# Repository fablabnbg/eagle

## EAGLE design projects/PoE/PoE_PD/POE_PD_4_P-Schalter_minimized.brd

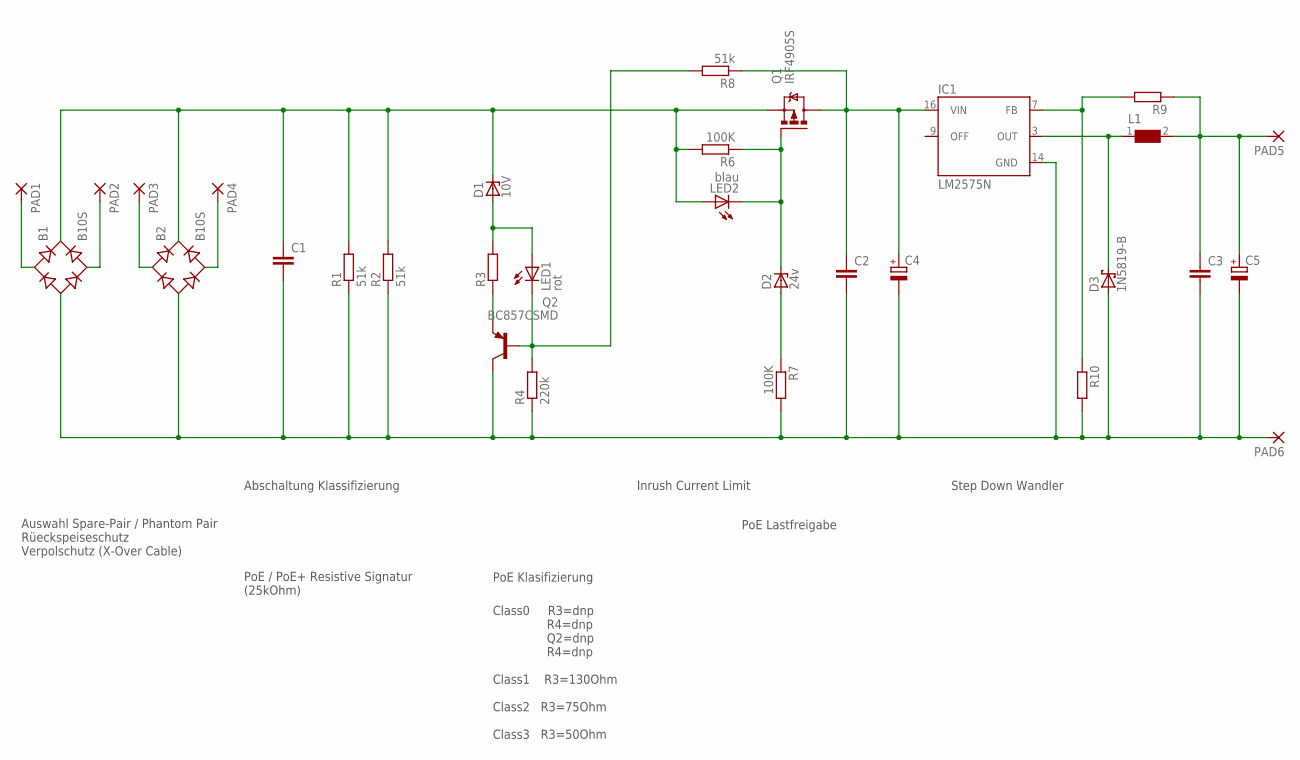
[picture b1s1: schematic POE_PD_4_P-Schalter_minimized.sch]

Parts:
B1, B2: B10S; MBS
C1, C2, C3: C-EUC0805; C0805
C4, C5: CPOL-EUE2.5-5; E2,5-5
D1: 10V; SOT23
D2: 24v; SOT23
D3: 1N5819-B; DO41-7.6
IC1: LM2575N; DIL16
L1: WE-PD2_S
LED1: rot; CHIP-LED0805
LED2: blau; CHIP-LED0805
PAD1, PAD2, PAD3, PAD4, PAD5, PAD6: 2,15/1,0
Q1: IRF4905S; D-PAK_TO252AA
Q2: BC857CSMD; SOT23-BEC
R1, R2, R8: 51k; R0603
R3, R9, R10: R-EU_0207/7; 0207/7
R4: 220k; R0603
R6, R7: 100K; R0603

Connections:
unnamed: B1.-, B2.-, C1.2, C2.2, C3.2, C4.-, C5.-, D3.A, IC1.14 (GND), PAD6.1, Q2.C, R1.1, R2.1, R4.1, R7.2, R10.2
unnamed: Q2.E, R3.1
unnamed: B1.AC1, PAD1.1
unnamed: LED1.C, Q2.B, R4.2, R8.2
unnamed: D1.1 (A), LED1.A, R3.2
unnamed: D2.1 (A), R7.1
unnamed: B1.+, B2.+, C1.1, D1.3 (C), LED2.A, Q1.3 (S), R1.2, R2.2, R6.2
unnamed: D2.3 (C), LED2.C, Q1.1 (G), R6.1
unnamed: D3.C, IC1.3 (OUT), L1.1
unnamed: C3.1, C5.+, L1.2, PAD5.1, R9.1
unnamed: C2.1, C4.+, IC1.16 (VIN), Q1.4 (D), R8.1
unnamed: IC1.7 (FB), R9.2, R10.1
unnamed: B1.AC2, PAD2.1
unnamed: B2.AC1, PAD3.1
unnamed: B2.AC2, PAD4.1

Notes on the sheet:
Auswahl Spare-Pair / Phantom Pair Rüeckspeiseschutz Verpolschutz (X-Over Cable)
Abschaltung Klassifizierung
PoE / PoE+ Resistive Signatur (25kOhm)
PoE Klasifizierung
Inrush Current Limit
PoE Lastfreigabe
Step Down Wandler
Class0 R3=dnp R4=dnp Q2=dnp R4=dnp Class1 R3=130Ohm Class2 R3=75Ohm Class3 R3=50Ohm

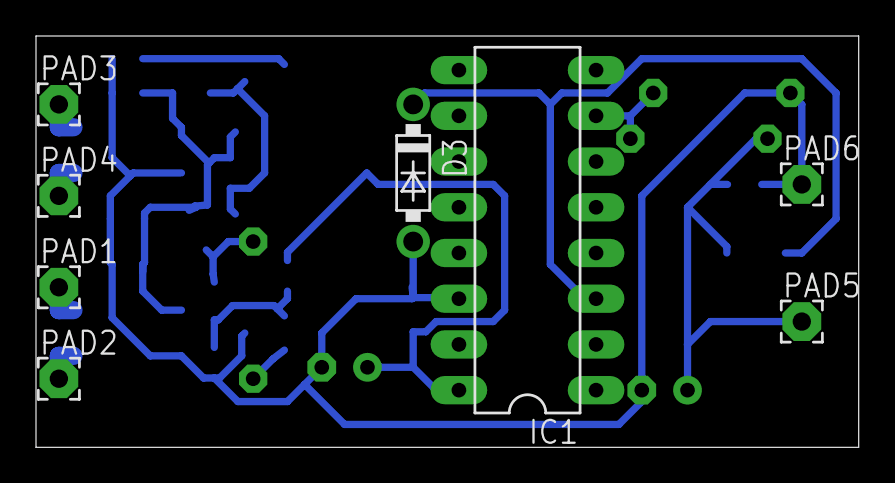
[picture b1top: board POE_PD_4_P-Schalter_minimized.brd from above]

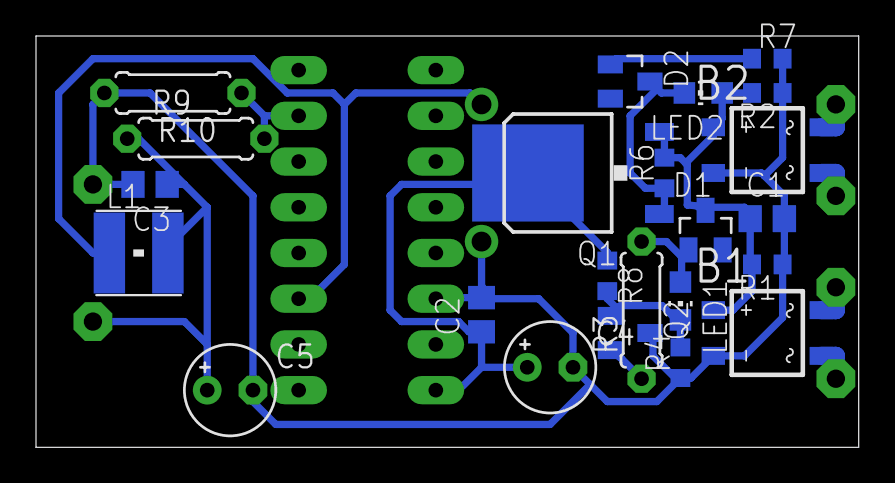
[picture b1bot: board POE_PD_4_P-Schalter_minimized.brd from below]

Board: 2 copper layers, 45.7 x 22.8 mm, 31 parts (23 on the bottom side), 15 nets.

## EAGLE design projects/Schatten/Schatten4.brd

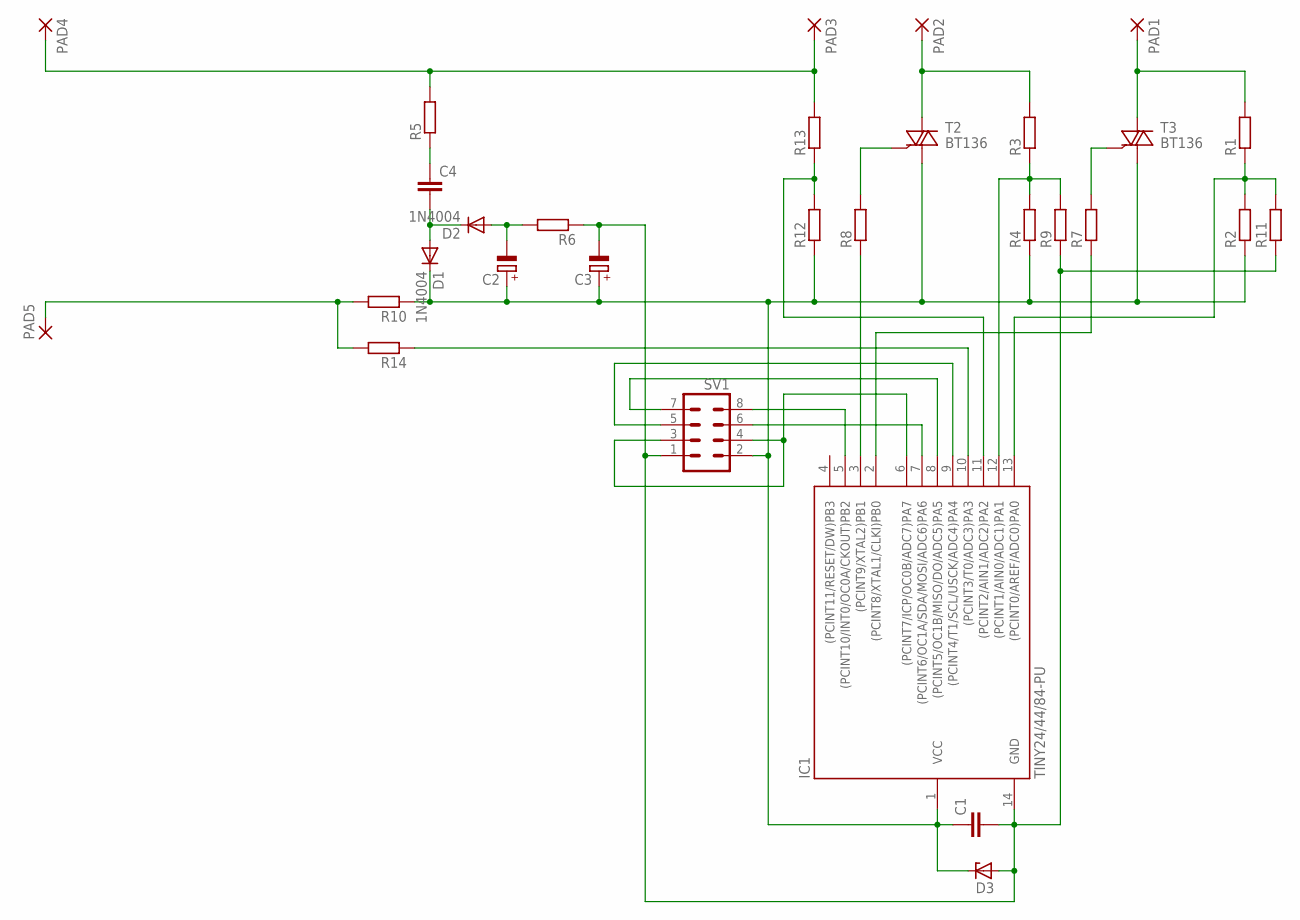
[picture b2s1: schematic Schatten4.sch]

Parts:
C1: C-EUC3225; C3225
C2, C3: CPOL-EUE5-8.5; E5-8,5
C4: C-EU150-064X183; C150-064X183
D1, D2: 1N4004; DO41-10
D3: ZENER-DIODEZD-7.5; ZDIO-7.5
IC1: TINY24/44/84-PU; DIL14
PAD1, PAD2, PAD3, PAD4, PAD5: 1,6/0,9
R1, R2, R3, R4, R5, R6, R7, R8, R9, R10, R11, R12, R13, R14: R-EU_0207/10; 0207/10
SV1: MA04-2
T2, T3: BT136; TO220AB

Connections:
unnamed: PAD5.1, R10.2, R14.2
unnamed: IC1.13 ((PCINT0/AREF/ADC0)PA0), R1.1, R2.2, R11.2
unnamed: IC1.10 ((PCINT3/T0/ADC3)PA3), R14.1
unnamed: IC1.7 ((PCINT6/OC1A/SDA/MOSI/ADC6)PA6), SV1.6
unnamed: IC1.12 ((PCINT1/AIN0/ADC1)PA1), R3.1, R4.2, R9.2
unnamed: IC1.2 ((PCINT8/XTAL1/CLKI)PB0), R7.1
unnamed: PAD1.1, R1.2, T3.2 (A2)
unnamed: PAD2.1, R3.2, T2.2 (A2)
unnamed: IC1.3 ((PCINT9/XTAL2)PB1), R8.1
unnamed: IC1.8 ((PCINT5/OC1B/MISO/DO/ADC5)PA5), SV1.7
unnamed: R8.2, T2.3 (G)
unnamed: R7.2, T3.3 (G)
unnamed: IC1.11 ((PCINT2/AIN1/ADC2)PA2), R12.2, R13.1
unnamed: IC1.9 ((PCINT4/T1/SCL/USCK/ADC4)PA4), SV1.5
unnamed: IC1.5 ((PCINT10/INT0/OC0A/CKOUT)PB2), SV1.8
unnamed: IC1.6 ((PCINT7/ICP/OC0B/ADC7)PA7), SV1.3, SV1.4
unnamed: PAD3.1, PAD4.1, R5.2, R13.2
unnamed: C1.1, C2.+, C3.+, D1.C, D3.C, IC1.1 (VCC), R2.1, R4.1, R10.1, R12.1, SV1.2, T2.1 (A1), T3.1 (A1)
unnamed: C4.1, R5.1
unnamed: C4.2, D1.A, D2.C
unnamed: C2.-, D2.A, R6.2
unnamed: C1.2, C3.-, D3.A, IC1.14 (GND), R6.1, R9.1, R11.1, SV1.1

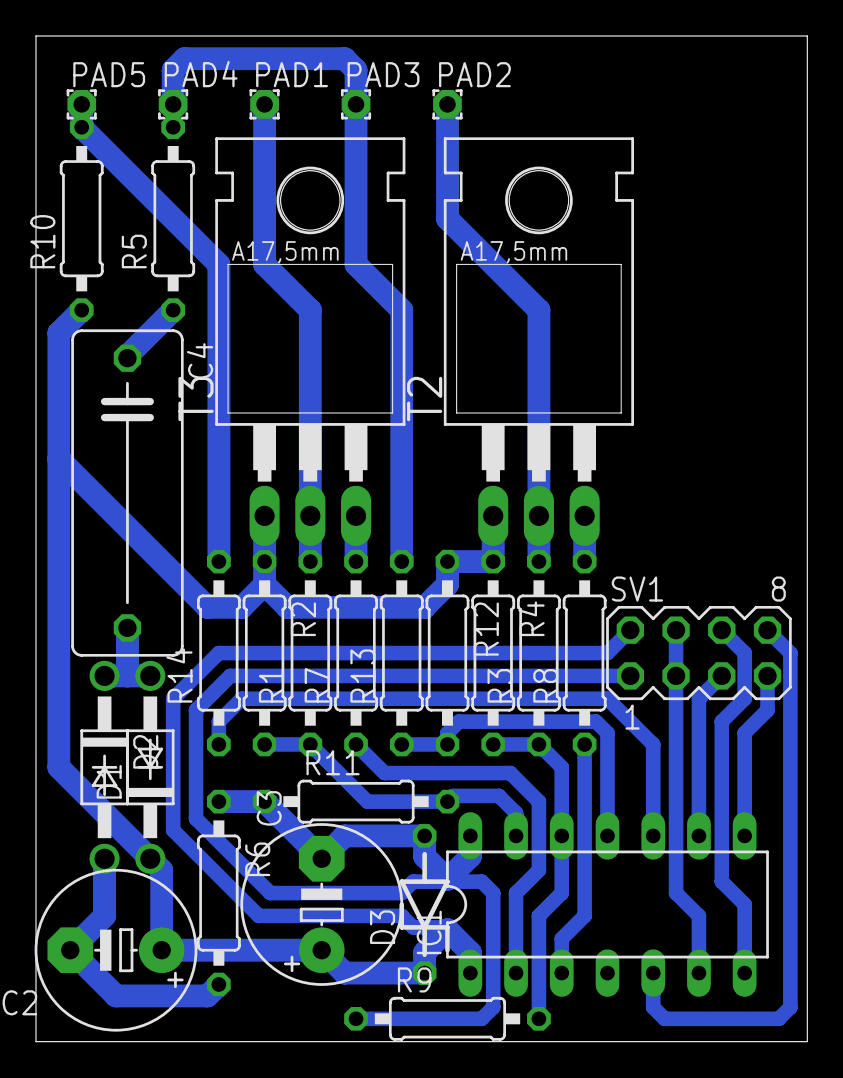
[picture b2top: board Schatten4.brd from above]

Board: 2 copper layers, 42.9 x 55.9 mm, 30 parts (1 on the bottom side), 22 nets.

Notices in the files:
parts and their libraries:
wuerth_elektronik_EAGLE: Copyright: Würth Elektronik eiSos
